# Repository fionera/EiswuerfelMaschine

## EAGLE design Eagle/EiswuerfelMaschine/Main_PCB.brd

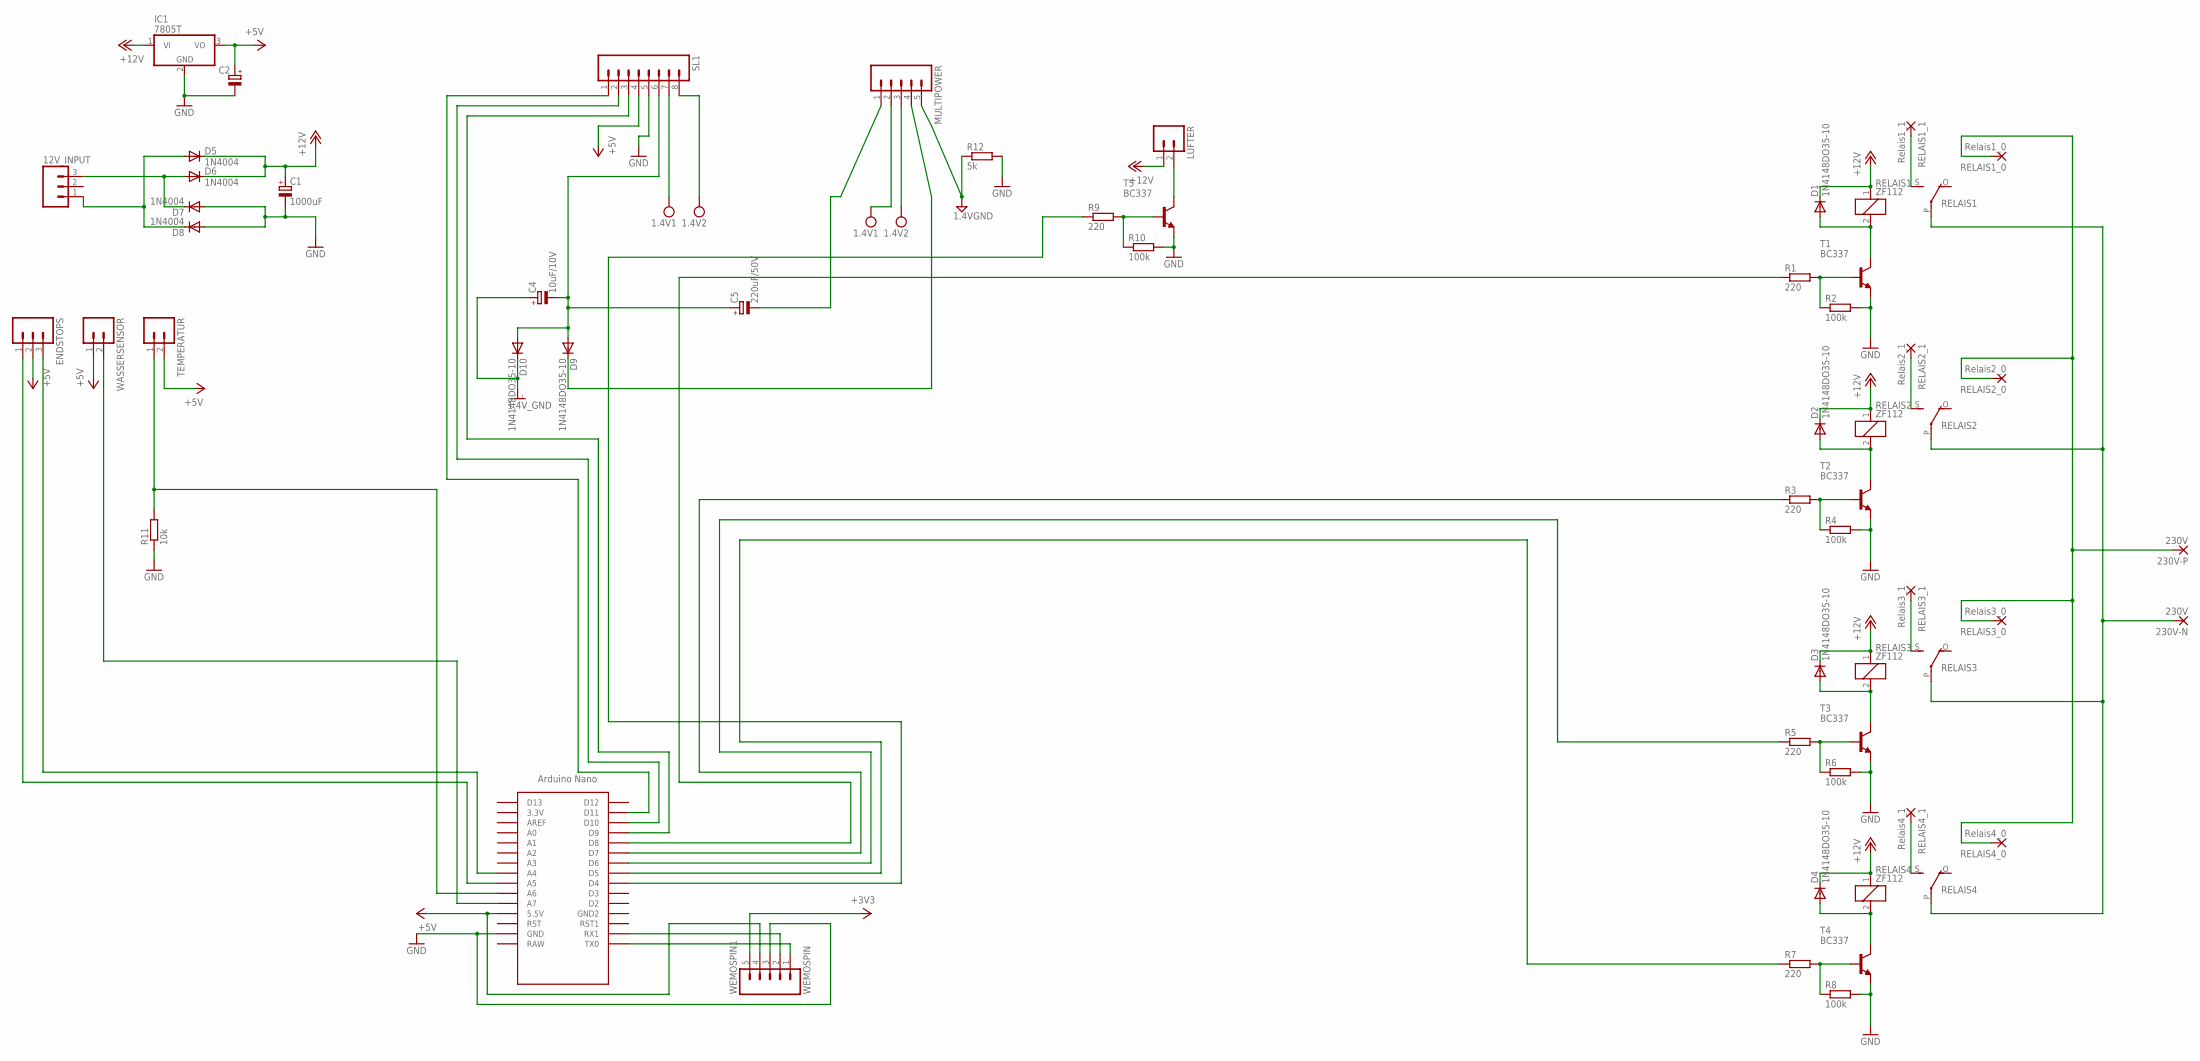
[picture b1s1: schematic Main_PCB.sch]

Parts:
12V_INPUT: M03; 03P
230V-N, 230V-P: 230V; 2,15/1,0
C1: 1000uF; E2,5-5
C2: CPOL-EUE2.5-4V; E2,5RE
C4: 10uF/10V; E2,5RE
C5: 220uF/50V; E2,5RE
D1, D2, D3, D4, D9, D10: 1N4148DO35-10; DO35-10
D5, D6, D7, D8: 1N4004; DO41-10
ENDSTOPS: M03; 03P
IC1: 7805T; TO220H
LÜFTER: M02; 02P
MULTIPOWER: M05; 05P
R1, R3, R5, R7, R9: 220; 0207/10
R2, R4, R6, R8, R10: 100k; 0207/10
R11: 10k; 0207/10
R12: 5k; 0207/10
RELAIS1, RELAIS2, RELAIS3, RELAIS4: ZF112
RELAIS1_0: Relais1_0; 2,15/1,0
RELAIS1_1: Relais1_1; 2,15/1,0
RELAIS2_0: Relais2_0; 2,15/1,0
RELAIS2_1: Relais2_1; 2,15/1,0
RELAIS3_0: Relais3_0; 2,15/1,0
RELAIS3_1: Relais3_1; 2,15/1,0
RELAIS4_0: Relais4_0; 2,15/1,0
RELAIS4_1: Relais4_1; 2,15/1,0
SL1: M08; 08P
T1, T2, T3, T4, T5: BC337; TO92
TEMPERATUR: M02; 02P
U$1: NANO
WASSERSENSOR: M02; 02P
WEMOSPIN1: WEMOSPIN; 05P

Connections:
+3V3: WEMOSPIN1.5
+5V: C2.+, ENDSTOPS.2, IC1.3 (VO), SL1.4, TEMPERATUR.2, U$1.5V (5.5V), WASSERSENSOR.1, WEMOSPIN1.4
+12V: C1.+, D1.C, D2.C, D3.C, D4.C, D5.C, D6.C, IC1.1 (VI), LÜFTER.1, RELAIS1.1, RELAIS2.1, RELAIS3.1, RELAIS4.1
GND: C1.-, C2.-, D7.A, D8.A, IC1.2 (GND), R2.2, R4.2, R6.2, R8.2, R10.2, R11.1, R12.2, SL1.5, T1.1 (E), T2.1 (E), T3.1 (E), T4.1 (E), T5.1 (E), U$1.GND, WEMOSPIN1.3
GND1: MULTIPOWER.5, R12.1
GNDI: C4.+, D10.C
unnamed: RELAIS4.S, RELAIS4_1.1
unnamed: D2.A, RELAIS2.2, T2.3 (C)
unnamed: D1.A, RELAIS1.2, T1.3 (C)
unnamed: R1.2, R2.1, T1.2 (B)
unnamed: RELAIS2.S, RELAIS2_1.1
unnamed: R3.2, R4.1, T2.2 (B)
unnamed: RELAIS3.S, RELAIS3_1.1
unnamed: D3.A, RELAIS3.2, T3.3 (C)
unnamed: R5.2, R6.1, T3.2 (B)
unnamed: RELAIS1.S, RELAIS1_1.1
unnamed: D4.A, RELAIS4.2, T4.3 (C)
unnamed: R7.2, R8.1, T4.2 (B)
unnamed: 230V-P.1, RELAIS1_0.1, RELAIS2_0.1, RELAIS3_0.1, RELAIS4_0.1
unnamed: R1.1, U$1.D8
unnamed: R3.1, U$1.D7
unnamed: R5.1, U$1.D6
unnamed: R7.1, U$1.D5
unnamed: R9.1, U$1.D4
unnamed: R11.2, TEMPERATUR.1, U$1.A6
unnamed: U$1.A7, WASSERSENSOR.2
unnamed: 12V_INPUT.3, D6.A, D7.C
unnamed: 12V_INPUT.1, D5.A, D8.C
unnamed: R9.2, R10.1, T5.2 (B)
unnamed: LÜFTER.2, T5.3 (C)
unnamed: U$1.RX1, WEMOSPIN1.2
unnamed: C4.-, C5.+, D9.A, D10.A, SL1.6
unnamed: SL1.3, U$1.D9
unnamed: SL1.2, U$1.D10
unnamed: SL1.1, U$1.D11
unnamed: U$1.TX0, WEMOSPIN1.1
unnamed: C5.-, MULTIPOWER.1
unnamed: D9.C, MULTIPOWER.4
unnamed: 230V-N.1, RELAIS1.P, RELAIS2.P, RELAIS3.P, RELAIS4.P
unnamed: ENDSTOPS.3, U$1.A4
unnamed: ENDSTOPS.1, U$1.A5
VCC: MULTIPOWER.2, SL1.7
VDD: MULTIPOWER.3, SL1.8

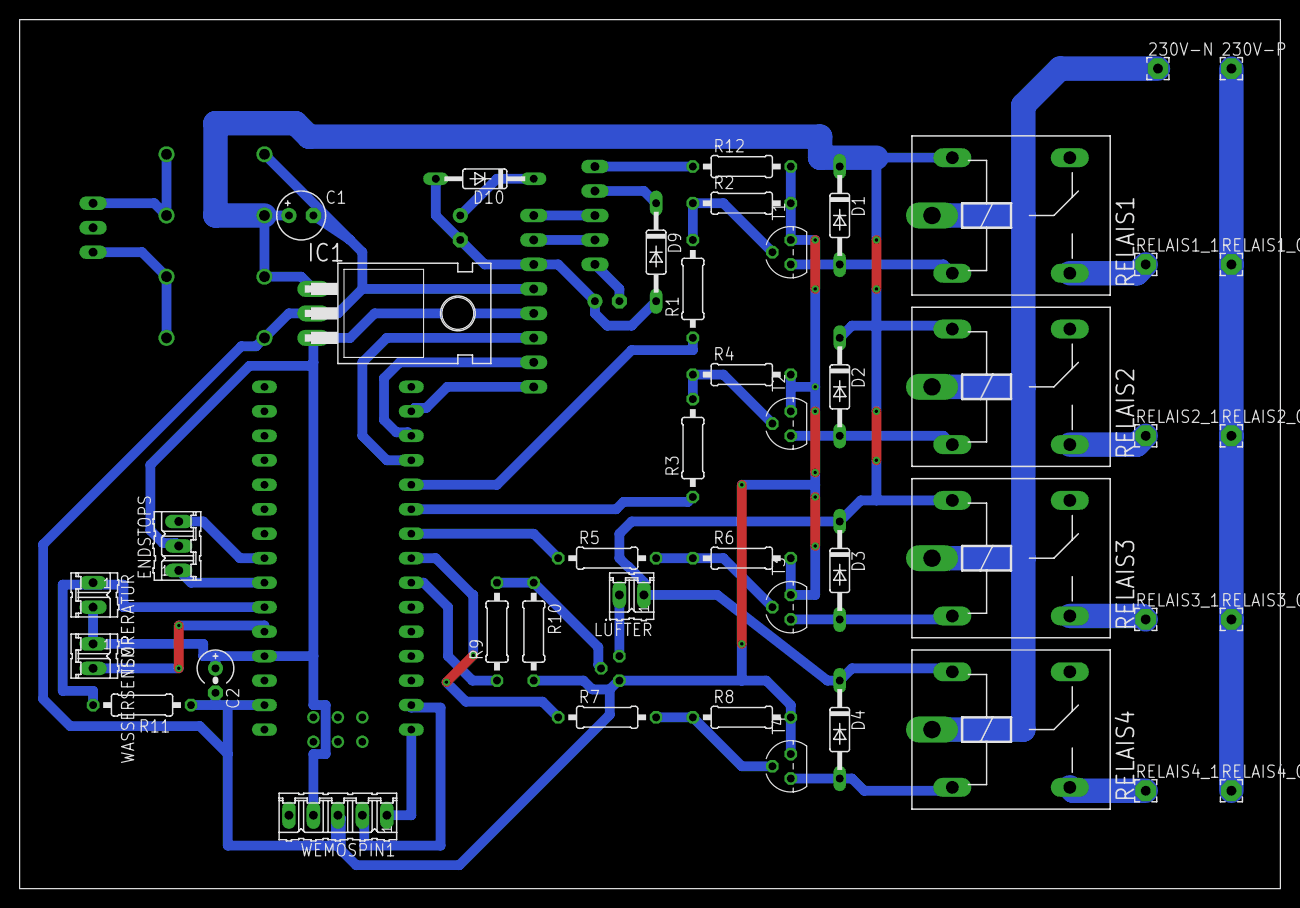
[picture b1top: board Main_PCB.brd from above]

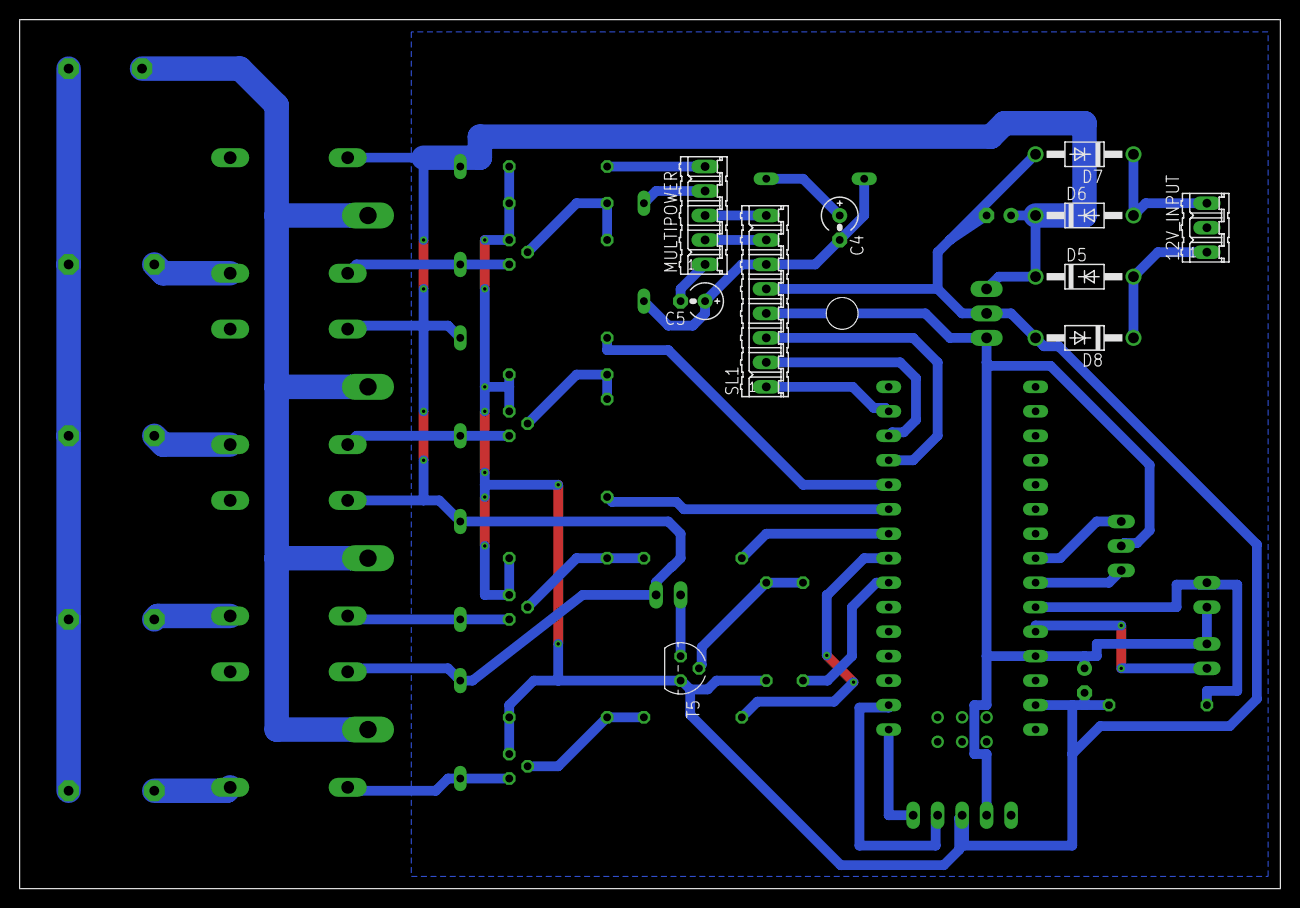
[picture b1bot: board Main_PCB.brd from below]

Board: 2 copper layers, 130.8 x 90.2 mm, 55 parts (10 on the bottom side), 42 nets.
